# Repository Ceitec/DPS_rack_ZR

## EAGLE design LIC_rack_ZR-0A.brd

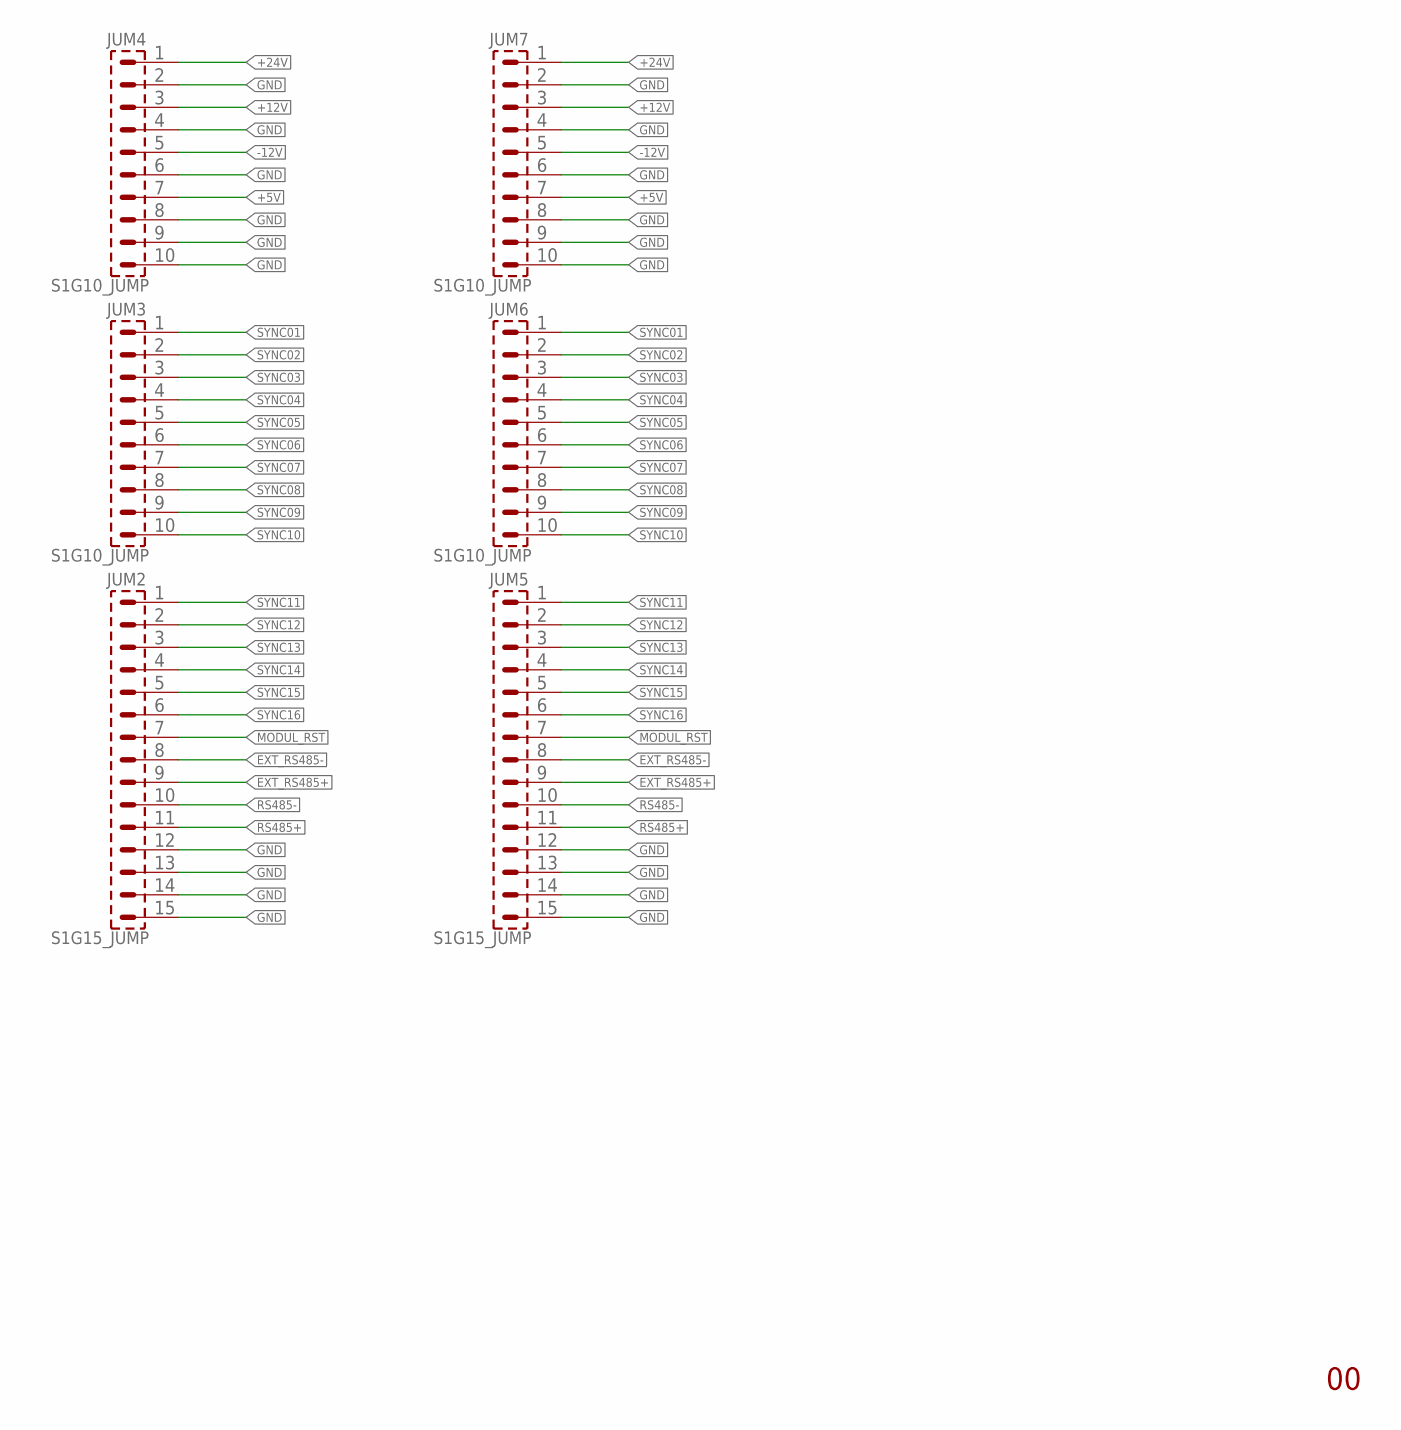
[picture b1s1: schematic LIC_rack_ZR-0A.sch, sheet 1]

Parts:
JUM2, JUM5: S1G15_JUMP; S1G15_JU
JUM3, JUM4, JUM6, JUM7: S1G10_JUMP; S1G10_JU

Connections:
+5V: JUM4.7, JUM7.7; also elsewhere on the board
+12V: JUM4.3, JUM7.3; also elsewhere on the board
+24V: JUM4.1, JUM7.1; also elsewhere on the board
-12V: JUM4.5, JUM7.5; also elsewhere on the board
EXT_RS485+: JUM2.9, JUM5.9
EXT_RS485-: JUM2.8, JUM5.8
GND: JUM2.12, JUM2.13, JUM2.14, JUM2.15, JUM4.2, JUM4.4, JUM4.6, JUM4.8, JUM4.9, JUM4.10, JUM5.12, JUM5.13, JUM5.14, JUM5.15, JUM7.2, JUM7.4, JUM7.6, JUM7.8, JUM7.9, JUM7.10; also elsewhere on the board
MODUL_RST: JUM2.7, JUM5.7; also elsewhere on the board
RS485+: JUM2.11, JUM5.11; also elsewhere on the board
RS485-: JUM2.10, JUM5.10; also elsewhere on the board
SYNC01: JUM3.1, JUM6.1
SYNC02: JUM3.2, JUM6.2
SYNC03: JUM3.3, JUM6.3
SYNC04: JUM3.4, JUM6.4
SYNC05: JUM3.5, JUM6.5
SYNC06: JUM3.6, JUM6.6
SYNC07: JUM3.7, JUM6.7
SYNC08: JUM3.8, JUM6.8
SYNC09: JUM3.9, JUM6.9
SYNC10: JUM3.10, JUM6.10
SYNC11: JUM2.1, JUM5.1
SYNC12: JUM2.2, JUM5.2
SYNC13: JUM2.3, JUM5.3
SYNC14: JUM2.4, JUM5.4
SYNC15: JUM2.5, JUM5.5
SYNC16: JUM2.6, JUM5.6

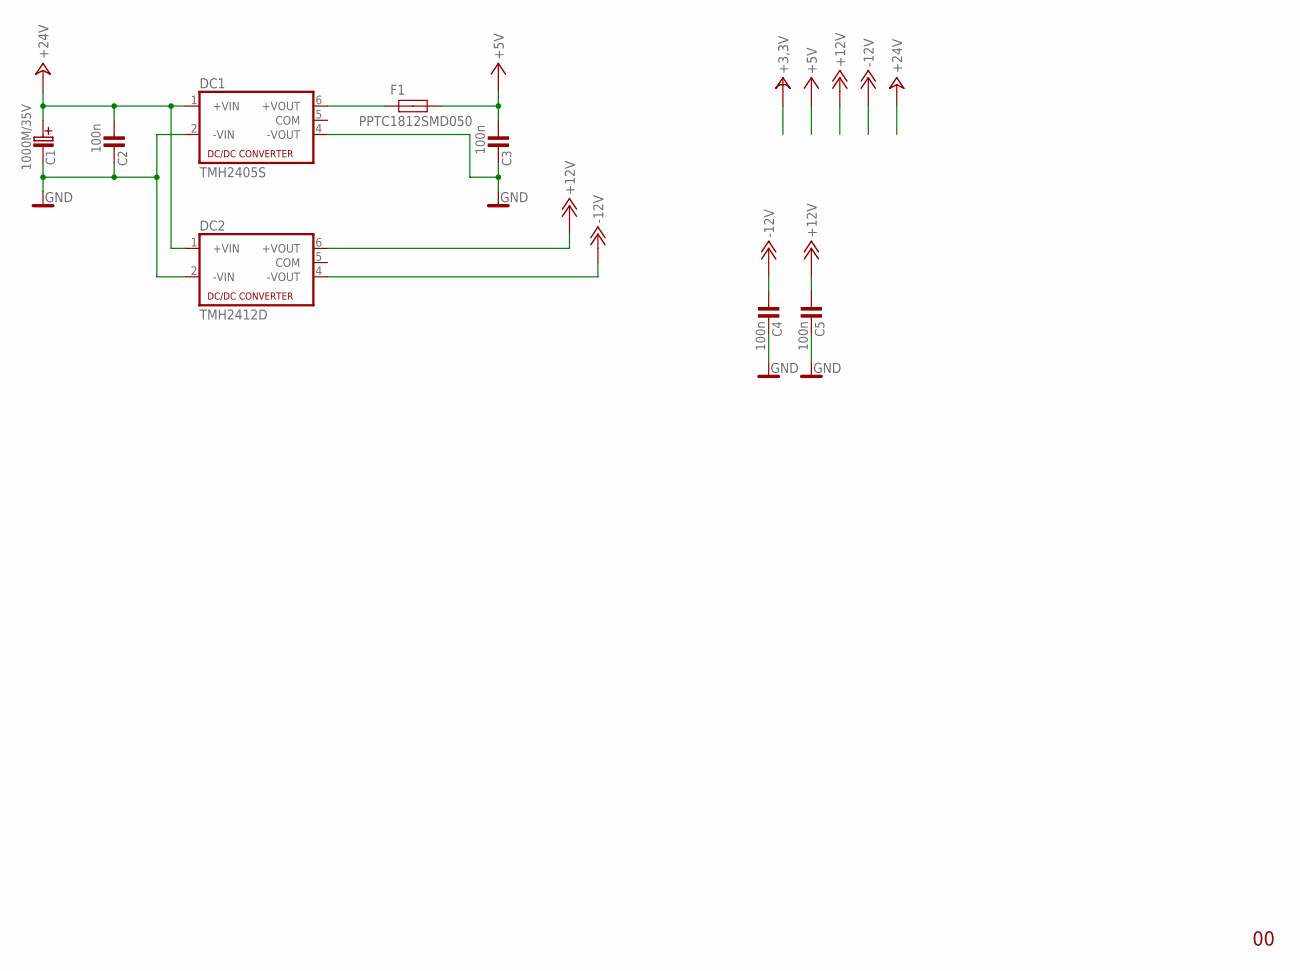
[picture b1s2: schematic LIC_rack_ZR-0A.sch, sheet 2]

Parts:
C1: 1000M/35V; C_EL_5+
C2, C3, C4, C5: 100n; 1206
DC1: TMH2405S; NMA
DC2: TMH2412D; NMA
F1: PPTC1812SMD050; R1812

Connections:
+5V: C3.1, F1.2; also elsewhere on the board
+12V: C5.1, DC2.6 (+VOUT); also elsewhere on the board
+24V: C1.C+ (C_EL+), C2.1, DC1.1 (+VIN), DC2.1 (+VIN); also elsewhere on the board
-12V: C4.1, DC2.4 (-VOUT); also elsewhere on the board
GND: C1.C- (C_EL-), C2.2, C3.2, C4.2, C5.2, DC1.2 (-VIN), DC1.4 (-VOUT), DC2.2 (-VIN); also elsewhere on the board
unnamed: DC1.6 (+VOUT), F1.1

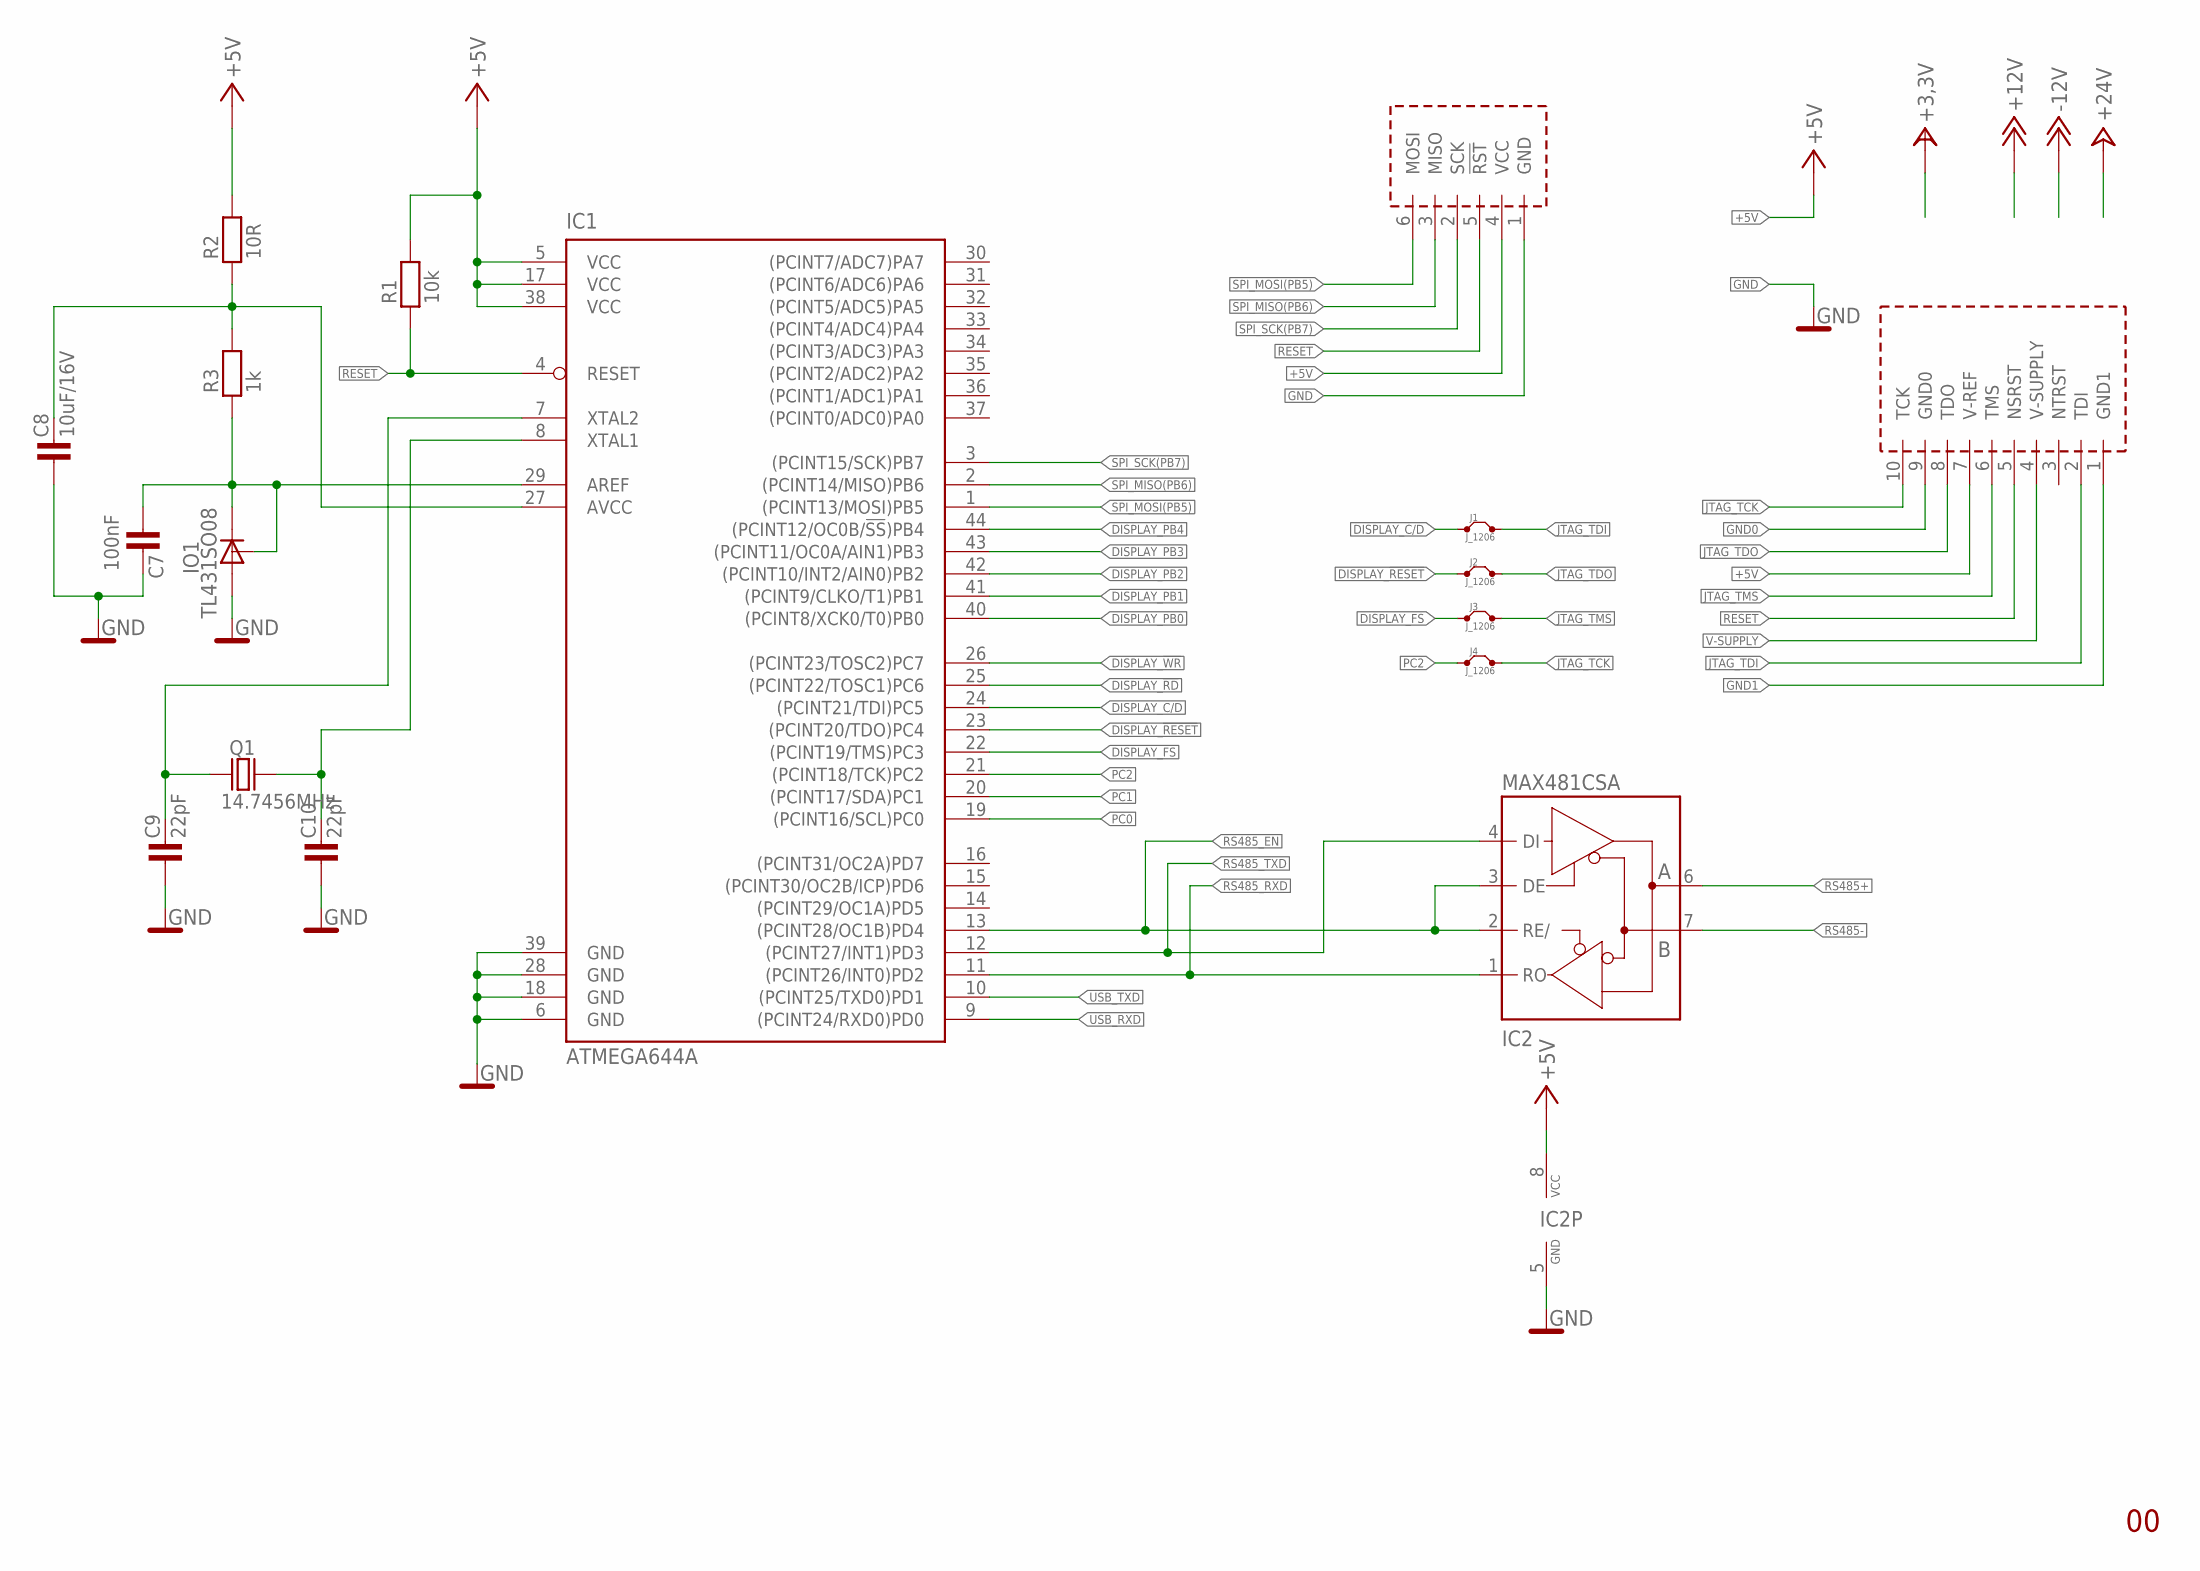
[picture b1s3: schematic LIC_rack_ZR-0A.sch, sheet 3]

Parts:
C7: 100nF; 1206
C8: 10uF/16V; 1206
C9, C10: 22pF; 0805
IC1: ATMEGA644A; TQFP44
IC2: MAX481CSA; SO08
IO1: TL431SO08; SO08
J1, J2, J3, J4: J_1206; 1206
Q1: 14.7456MHz; HC-49U
R1: 10k; 1206
R2: 10R; 1206
R3: 1k; 1206
U$1: AVR_PROG_JTAG; PSH02-10P
U$2: AVR_PROG_SPI; PSH02-06P

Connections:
0V: IC2.5 (GND)
+5V: IC1.5 (VCC), IC1.17 (VCC), IC1.38 (VCC), IC2.8 (VCC), R1.2, R2.2, U$1.7 (V-REF), U$2.4 (VCC); also elsewhere on the board
DISPLAY_!RD: IC1.25 ((PCINT22/TOSC1)PC6); also elsewhere on the board
DISPLAY_!RESET: IC1.23 ((PCINT20/TDO)PC4), J2.1; also elsewhere on the board
DISPLAY_!WR: IC1.26 ((PCINT23/TOSC2)PC7); also elsewhere on the board
DISPLAY_C/D: IC1.24 ((PCINT21/TDI)PC5), J1.1; also elsewhere on the board
DISPLAY_FS: IC1.22 ((PCINT19/TMS)PC3), J3.1; also elsewhere on the board
DISPLAY_PB0: IC1.40 ((PCINT8/XCK0/T0)PB0); also elsewhere on the board
DISPLAY_PB1: IC1.41 ((PCINT9/CLKO/T1)PB1); also elsewhere on the board
DISPLAY_PB2: IC1.42 ((PCINT10/INT2/AIN0)PB2); also elsewhere on the board
DISPLAY_PB3: IC1.43 ((PCINT11/OC0A/AIN1)PB3); also elsewhere on the board
DISPLAY_PB4: IC1.44 ((PCINT12/OC0B/!SS!)PB4); also elsewhere on the board
GND: C7.1, C8.1, C9.1, C10.1, IC1.6 (GND), IC1.18 (GND), IC1.28 (GND), IC1.39 (GND), IO1.2 (A), U$2.1 (GND); also elsewhere on the board
GND0: U$1.9 (GND0)
GND1: U$1.1 (GND1)
JTAG_TCK: J4.2, U$1.10 (TCK)
JTAG_TDI: J1.2, U$1.2 (TDI)
JTAG_TDO: J2.2, U$1.8 (TDO)
JTAG_TMS: J3.2, U$1.6 (TMS)
MODUL_RST: IC1.14 ((PCINT29/OC1A)PD5); also elsewhere on the board
unnamed: C9.2, IC1.7 (XTAL2), Q1.1
unnamed: C10.2, IC1.8 (XTAL1), Q1.2
unnamed: C8.2, IC1.27 (AVCC), R2.1, R3.2
unnamed: C7.2, IC1.29 (AREF), IO1.1 (C), IO1.8 (R), R3.1
PC0: IC1.19 ((PCINT16/SCL)PC0)
PC1: IC1.20 ((PCINT17/SDA)PC1)
PC2: IC1.21 ((PCINT18/TCK)PC2), J4.1
RESET: IC1.4 (RESET), R1.1, U$1.5 (NSRST), U$2.5 (!RST)
RS485+: IC2.6 (A); also elsewhere on the board
RS485-: IC2.7 (B); also elsewhere on the board
RS485_EN: IC1.13 ((PCINT28/OC1B)PD4), IC2.2 (RE/), IC2.3 (DE)
RS485_RXD: IC1.11 ((PCINT26/INT0)PD2), IC2.1 (RO)
RS485_TXD: IC1.12 ((PCINT27/INT1)PD3), IC2.4 (DI)
SPI_MISO(PB6): IC1.2 ((PCINT14/MISO)PB6), U$2.3 (MISO); also elsewhere on the board
SPI_MOSI(PB5): IC1.1 ((PCINT13/MOSI)PB5), U$2.6 (MOSI); also elsewhere on the board
SPI_SCK(PB7): IC1.3 ((PCINT15/SCK)PB7), U$2.2 (SCK); also elsewhere on the board
USB_RXD: IC1.9 ((PCINT24/RXD0)PD0)
USB_TXD: IC1.10 ((PCINT25/TXD0)PD1)
V-SUPPLY: U$1.4 (V-SUPPLY)

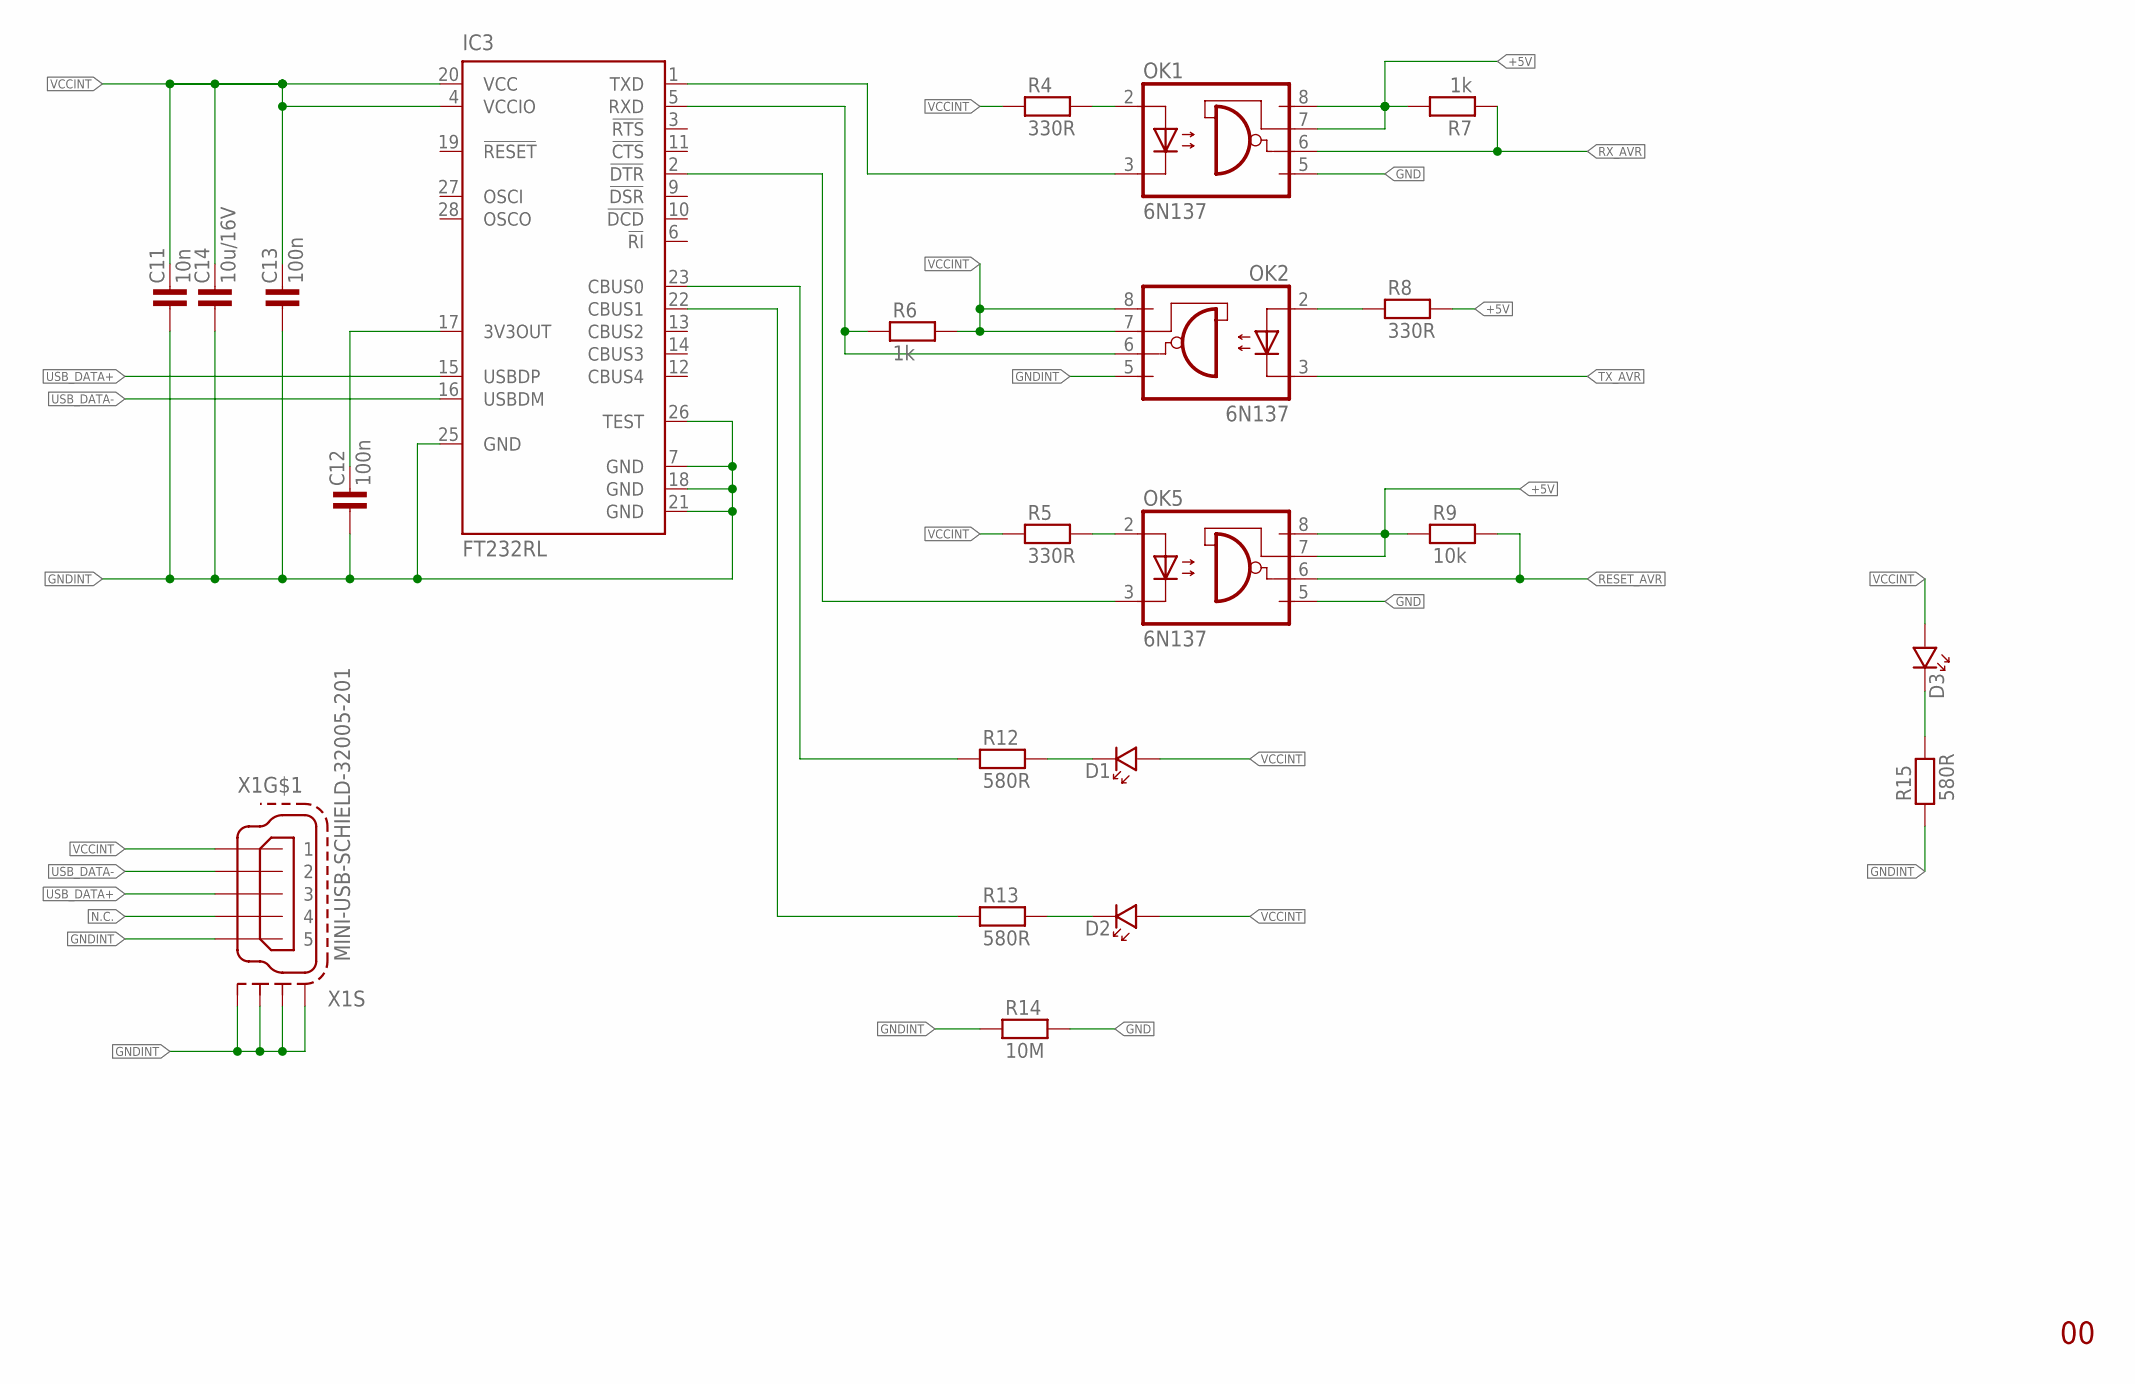
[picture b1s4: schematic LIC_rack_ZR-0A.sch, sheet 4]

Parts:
C11: 10n; 1206
C12, C13: 100n; 1206
C14: 10u/16V; 1206
D1, D2, D3: LED_1206; P1206
IC3: FT232RL; SSOP28
OK1, OK2, OK5: 6N137; DIL08
R4, R5, R8: 330R; 1206
R6, R7: 1k; 1206
R9: 10k; 1206
R12, R13, R15: 580R; 1206
R14: 10M; 1206
X1: MINI-USB-SCHIELD-32005-201; 32005-201

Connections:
+5V: OK1.7 (VE), OK1.8 (VCC), OK5.7 (VE), OK5.8 (VCC), R7.2, R8.2, R9.1; also elsewhere on the board
GND: OK1.5 (GND), OK5.5 (GND), R14.2; also elsewhere on the board
GNDINT: C11.1, C12.1, C13.1, C14.1, IC3.7 (GND), IC3.18 (GND), IC3.21 (GND), IC3.25 (GND), IC3.26 (TEST), OK2.5 (GND), R14.1, R15.1, X1.5, X1.M1 (S1), X1.M2 (S2), X1.M3 (S3), X1.M4 (S4)
unnamed: IC3.2 (!DTR), OK5.3 (C)
unnamed: OK1.2 (A), R4.2
unnamed: IC3.1 (TXD), OK1.3 (C)
unnamed: IC3.5 (RXD), OK2.6 (VO), R6.1
unnamed: OK2.2 (A), R8.1
unnamed: IC3.23 (CBUS0), R12.1
unnamed: IC3.22 (CBUS1), R13.1
unnamed: OK5.2 (A), R5.2
unnamed: D1.K, R12.2
unnamed: D2.K, R13.2
unnamed: D3.K, R15.2
unnamed: C12.2, IC3.17 (3V3OUT)
N.C.: X1.4
RESET_AVR: OK5.6 (VO), R9.2
RX_AVR: OK1.6 (VO), R7.1
TX_AVR: OK2.3 (C)
USB_DATA+: IC3.15 (USBDP), X1.3
USB_DATA-: IC3.16 (USBDM), X1.2
VCCINT: C11.2, C13.2, C14.2, D1.A, D2.A, D3.A, IC3.4 (VCCIO), IC3.20 (VCC), OK2.7 (VE), OK2.8 (VCC), R4.1, R5.1, R6.2, X1.1

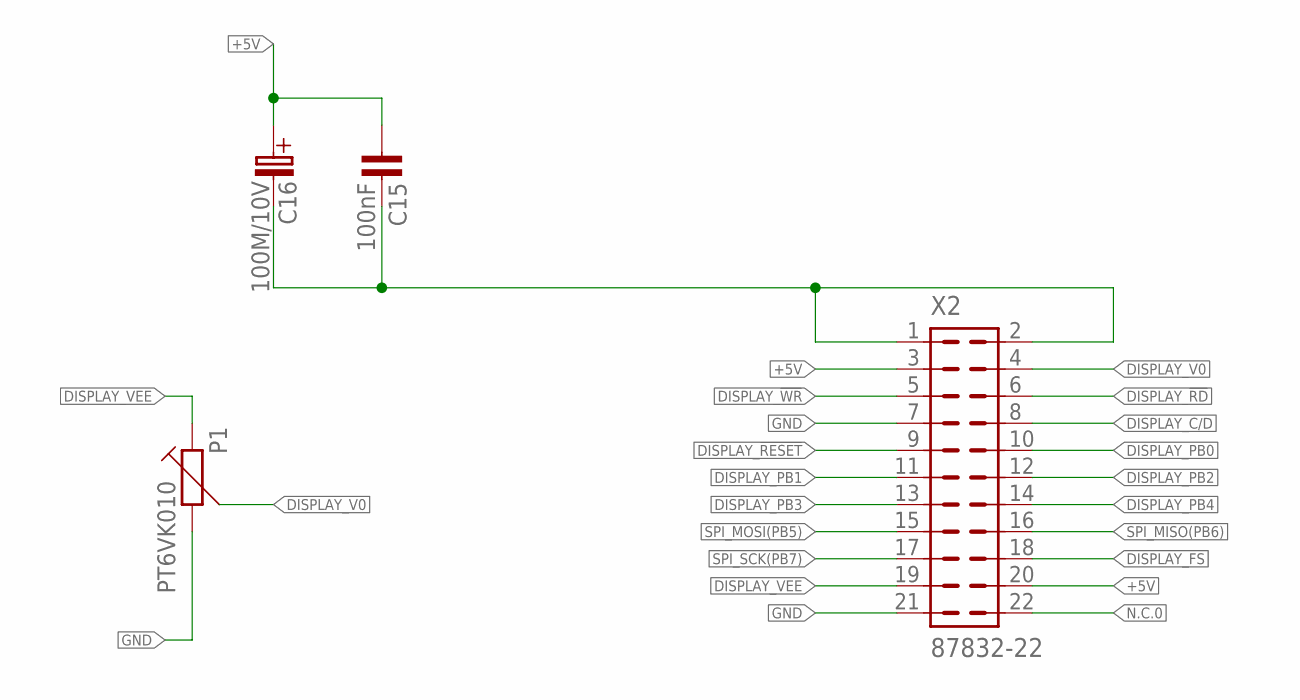
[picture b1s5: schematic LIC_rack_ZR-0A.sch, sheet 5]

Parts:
C15: 100nF; 1206
C16: 100M/10V; C_EL_2
P1: PT6VK010; PT6V
X2: 87832-22

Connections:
+5V: C15.1, C16.C+ (C_EL+), X2.3, X2.20; also elsewhere on the board
DISPLAY_!RD: X2.6; also elsewhere on the board
DISPLAY_!RESET: X2.9; also elsewhere on the board
DISPLAY_!WR: X2.5; also elsewhere on the board
DISPLAY_C/D: X2.8; also elsewhere on the board
DISPLAY_FS: X2.18; also elsewhere on the board
DISPLAY_PB0: X2.10; also elsewhere on the board
DISPLAY_PB1: X2.11; also elsewhere on the board
DISPLAY_PB2: X2.12; also elsewhere on the board
DISPLAY_PB3: X2.13; also elsewhere on the board
DISPLAY_PB4: X2.14; also elsewhere on the board
DISPLAY_V0: P1.3, X2.4
DISPLAY_VEE: P1.1, X2.19
GND: C15.2, C16.C- (C_EL-), P1.2, X2.1, X2.2, X2.7, X2.21; also elsewhere on the board
N.C.0: X2.22
SPI_MISO(PB6): X2.16; also elsewhere on the board
SPI_MOSI(PB5): X2.15; also elsewhere on the board
SPI_SCK(PB7): X2.17; also elsewhere on the board

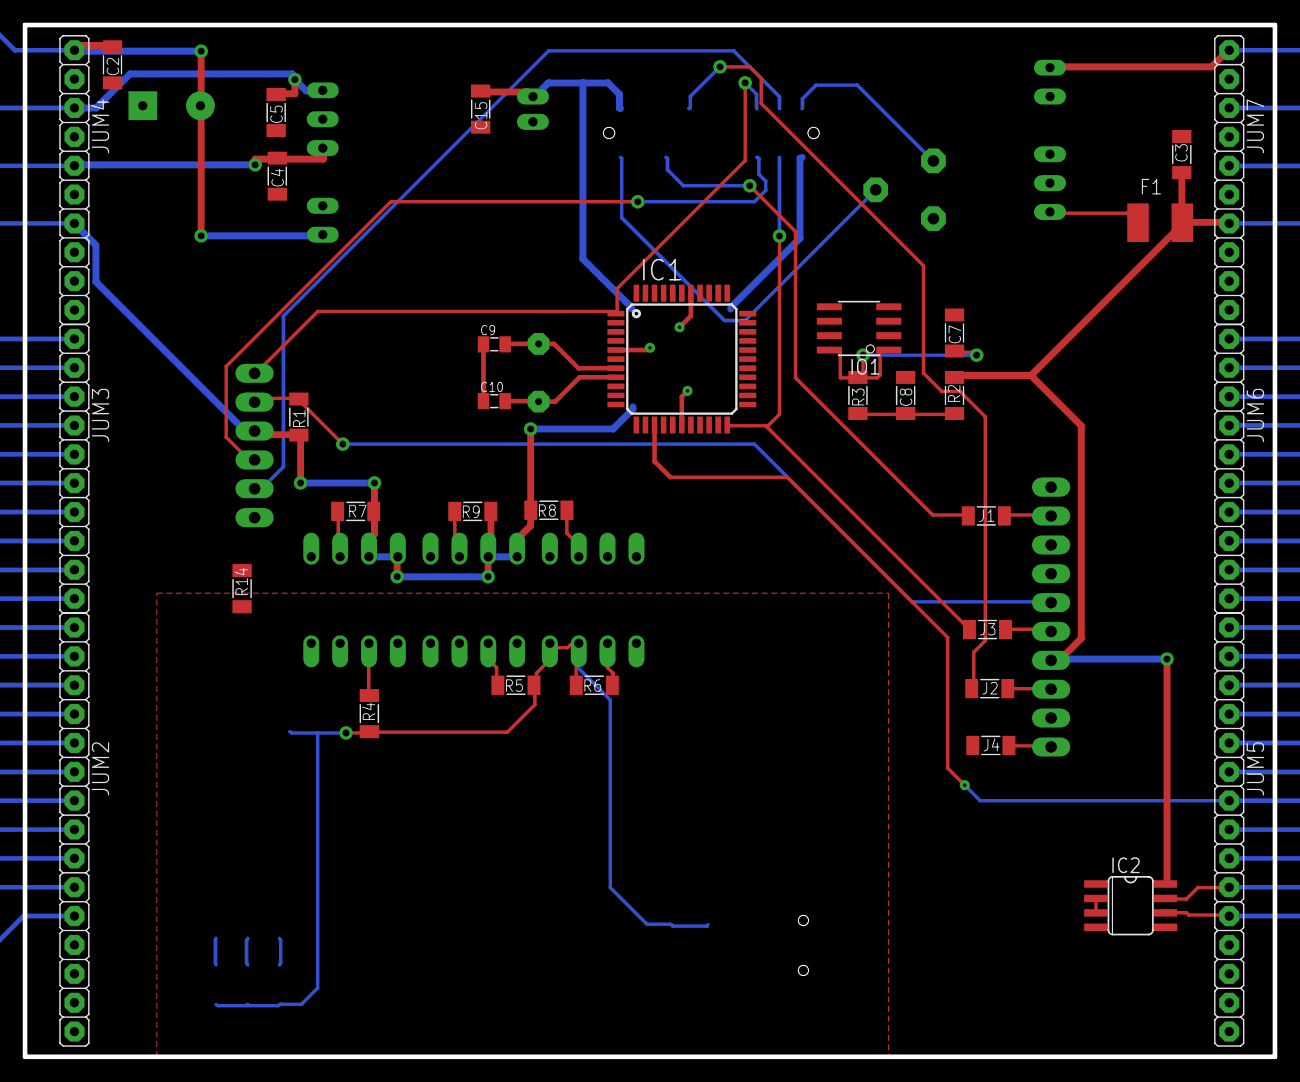
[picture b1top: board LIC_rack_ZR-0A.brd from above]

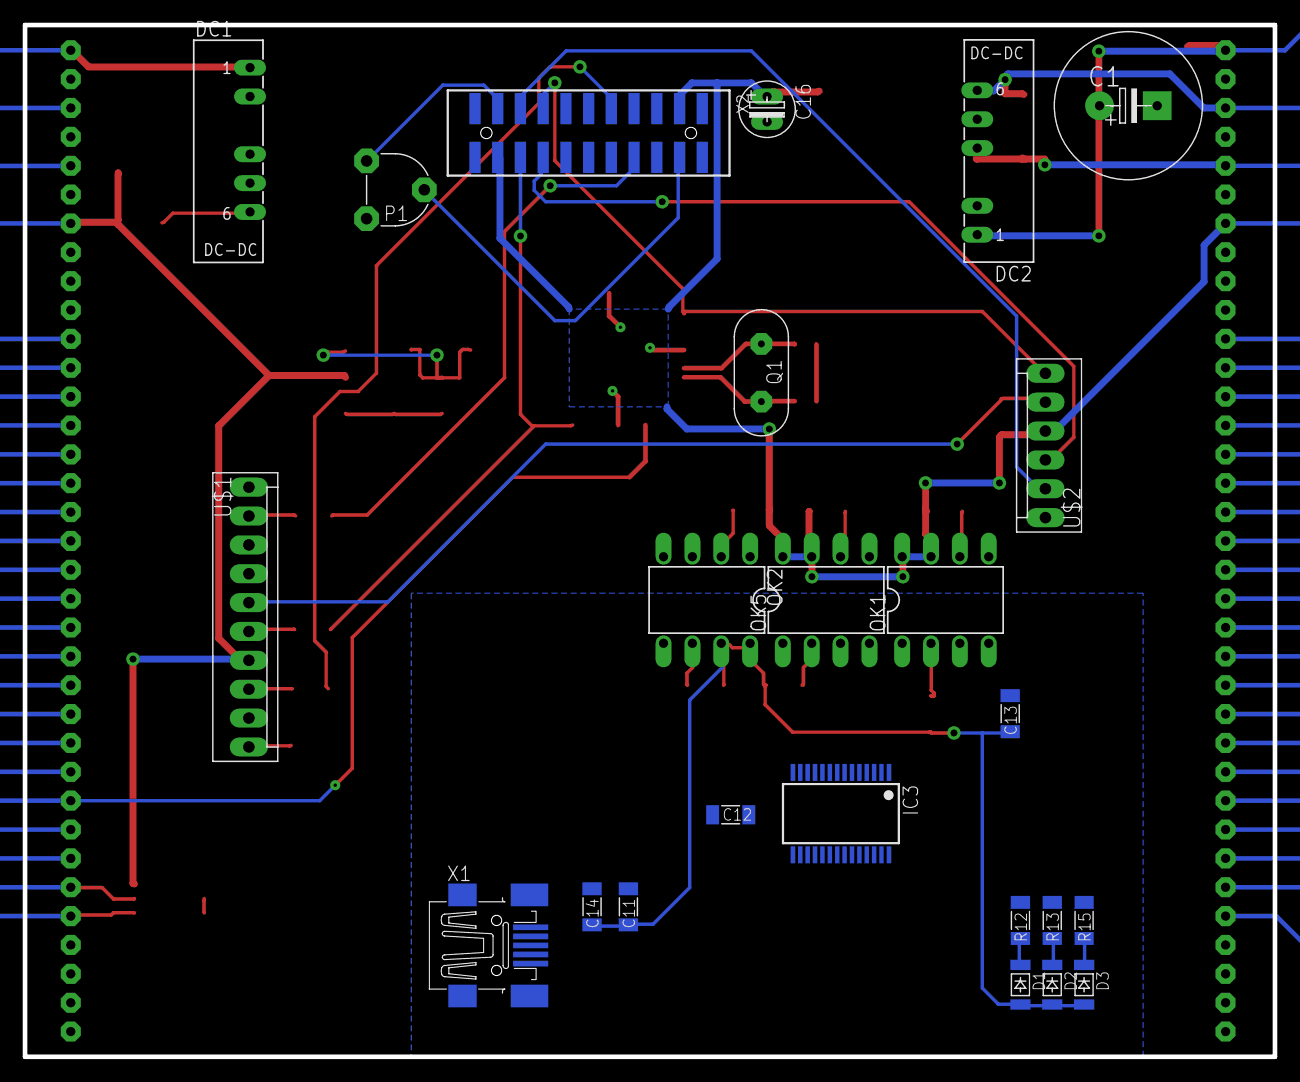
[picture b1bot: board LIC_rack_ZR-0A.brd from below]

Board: 2 copper layers, 110.0 x 90.8 mm, 57 parts (24 on the bottom side), 73 nets.

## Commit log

2015-11-10 :tada: Added .gitattributes & .gitignore files
2015-11-10 Základní řídící jednotka
2015-11-16 Dalsi upravy
    Pridan mikrokontrolér a další řídící prvky ještě je nutné přidat
    DMMT5401 a DMG2305UX proti přepólování
2015-11-18 Pridan popisek
    Pridan jenom popisek pro vyber displeje...
2015-11-22 Uprava desek
    Uprava desek a pouziti autorouteru pro verzi 01
2015-11-30 Uprava desky
    Pridán signál pro resetování modulů....

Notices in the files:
parts and their libraries:
Copyright (C) PaJa 2011-2014
Copyright (C) PaJa 2003-2009
Copyright (C) PaJa 2001-2014
